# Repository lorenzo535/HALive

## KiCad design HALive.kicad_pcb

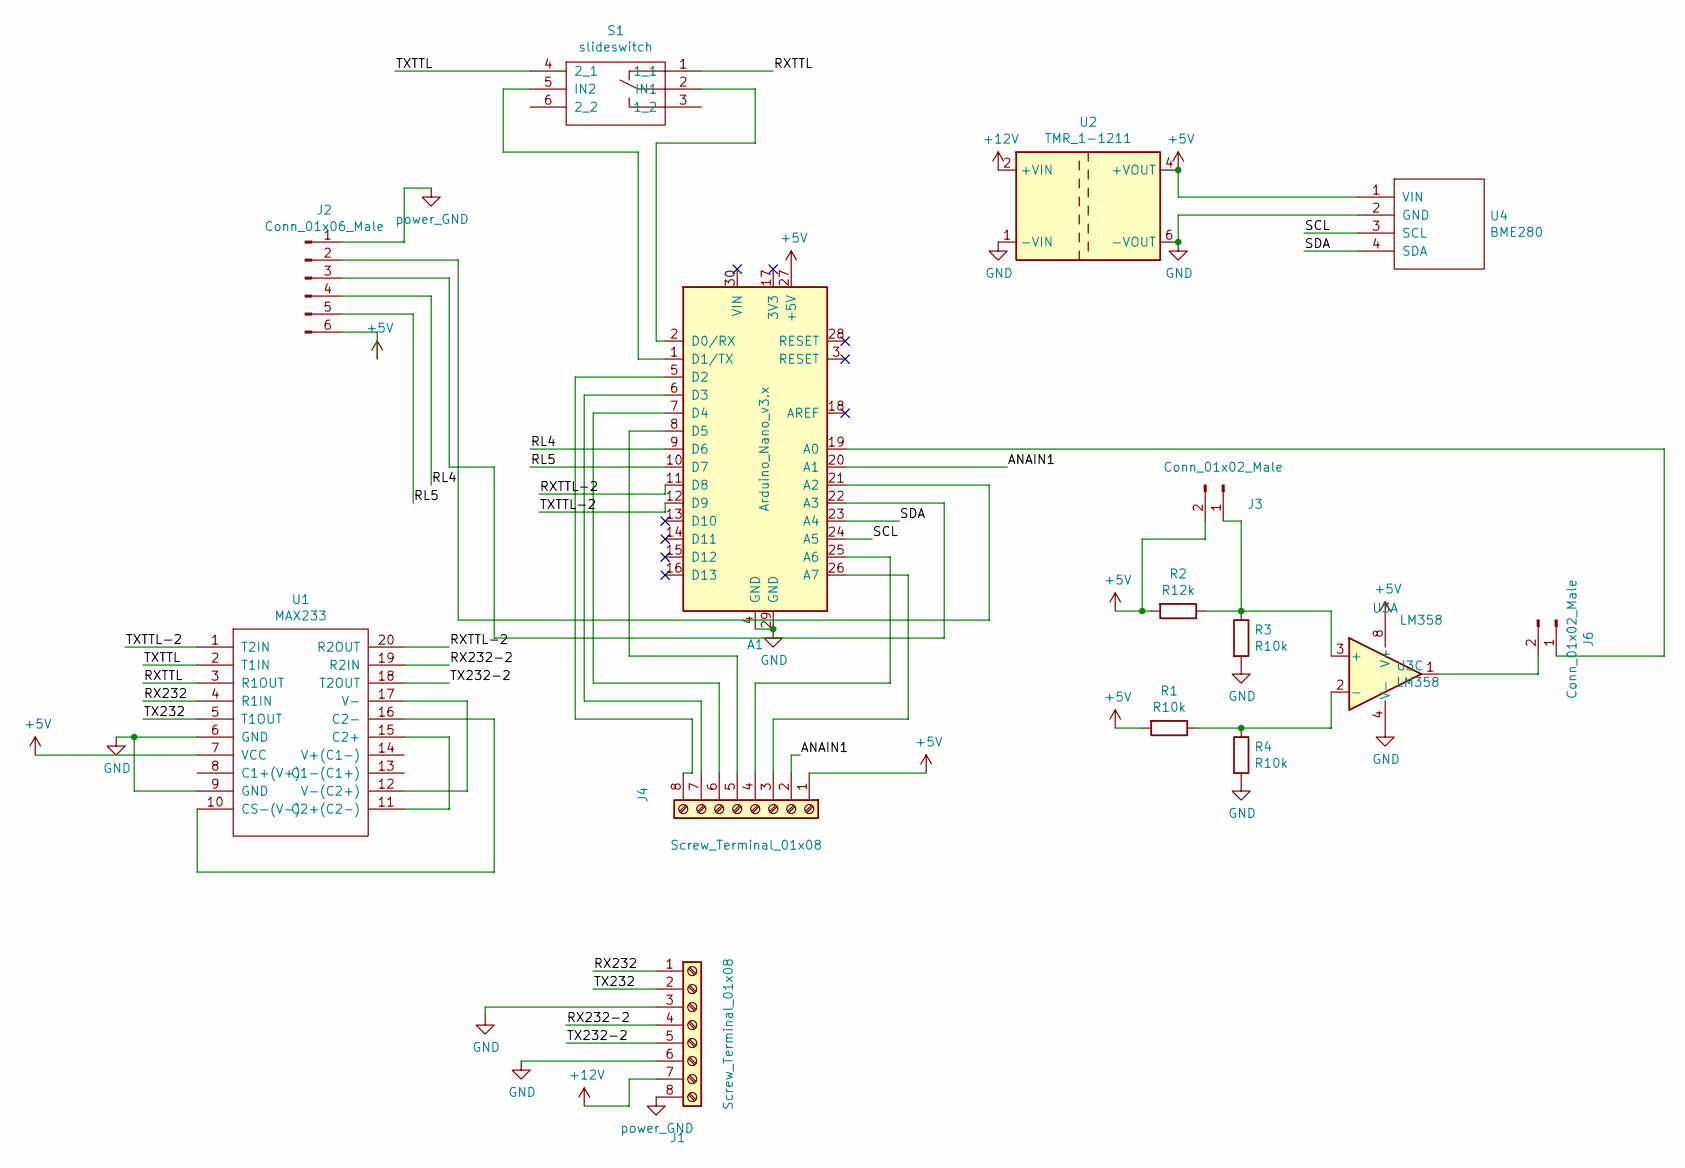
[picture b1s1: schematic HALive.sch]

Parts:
A1: Arduino_Nano_v3.x; Arduino_Nano
J1, J4: Screw_Terminal_01x08; PhoenixContact_MCV_1,5_8-G-3.5_1x08_P3.50mm_Vertical
J2: Conn_01x06_Male; PinHeader_1x06_P2.54mm_Vertical
J3, J6: Conn_01x02_Male; PinHeader_1x02_P2.54mm_Vertical
R1, R3, R4: R10k; R_Axial_DIN0207_L6.3mm_D2.5mm_P10.16mm_Horizontal
R2: R12k; R_Axial_DIN0207_L6.3mm_D2.5mm_P10.16mm_Horizontal
S1: slideswitch; slide_sxitch_TE_ASE2204
U1: MAX233; DIP-20_W7.62mm
U2: TMR_1-1211; Converter_DCDC_TRACO_TMR-1-xxxx_Single_THT
U3: LM358; DIP-8_W7.62mm
U4: BME280

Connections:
+5V: A1.27 (+5V), J2.6, J3.2, J4.1, R1.2, R2.2, U1.7 (VCC), U2.4 (+VOUT), U3.8 (V+), U4.1 (VIN)
+12V: J1.7, U2.2 (+VIN)
/ANAIN1: A1.20 (A1), J4.2
/RL4: A1.9 (D6), J2.4
/RL5: A1.10 (D7), J2.5
/RX232: J1.1, U1.4 (R1IN)
/RX232-2: J1.4, U1.19 (R2IN)
/RXTTL: S1.1 (1_1), U1.3 (R1OUT)
/RXTTL-2: A1.11 (D8), U1.20 (R2OUT)
/SCL: A1.24 (A5), U4.3 (SCL)
/SDA: A1.23 (A4), U4.4 (SDA)
/TX232: J1.2, U1.5 (T1OUT)
/TX232-2: J1.5, U1.18 (T2OUT)
/TXTTL: S1.4 (2_1), U1.2 (T1IN)
/TXTTL-2: A1.12 (D9), U1.1 (T2IN)
unnamed: A1.1 (D1/TX), S1.5 (IN2)
unnamed: A1.2 (D0/RX), S1.2 (IN1)
unnamed: A1.5 (D2), J4.8
unnamed: A1.6 (D3), J4.7
unnamed: A1.7 (D4), J4.6
unnamed: A1.8 (D5), J4.5
unnamed: A1.19 (A0), J6.1
unnamed: A1.21 (A2), J2.2
unnamed: A1.22 (A3), J2.3
unnamed: A1.25 (A6), J4.4
unnamed: A1.26 (A7), J4.3
unnamed: J3.1, R2.1, R3.1, U3.3 (+)
unnamed: J6.2, U3.1
unnamed: R1.1, R4.1, U3.2 (-)
unnamed: U1.10 (CS-(V-)), U1.16 (C2-)
unnamed: U1.11 (C2+(C2-)), U1.15 (C2+)
unnamed: U1.12 (V-(C2+)), U1.17 (V-)

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
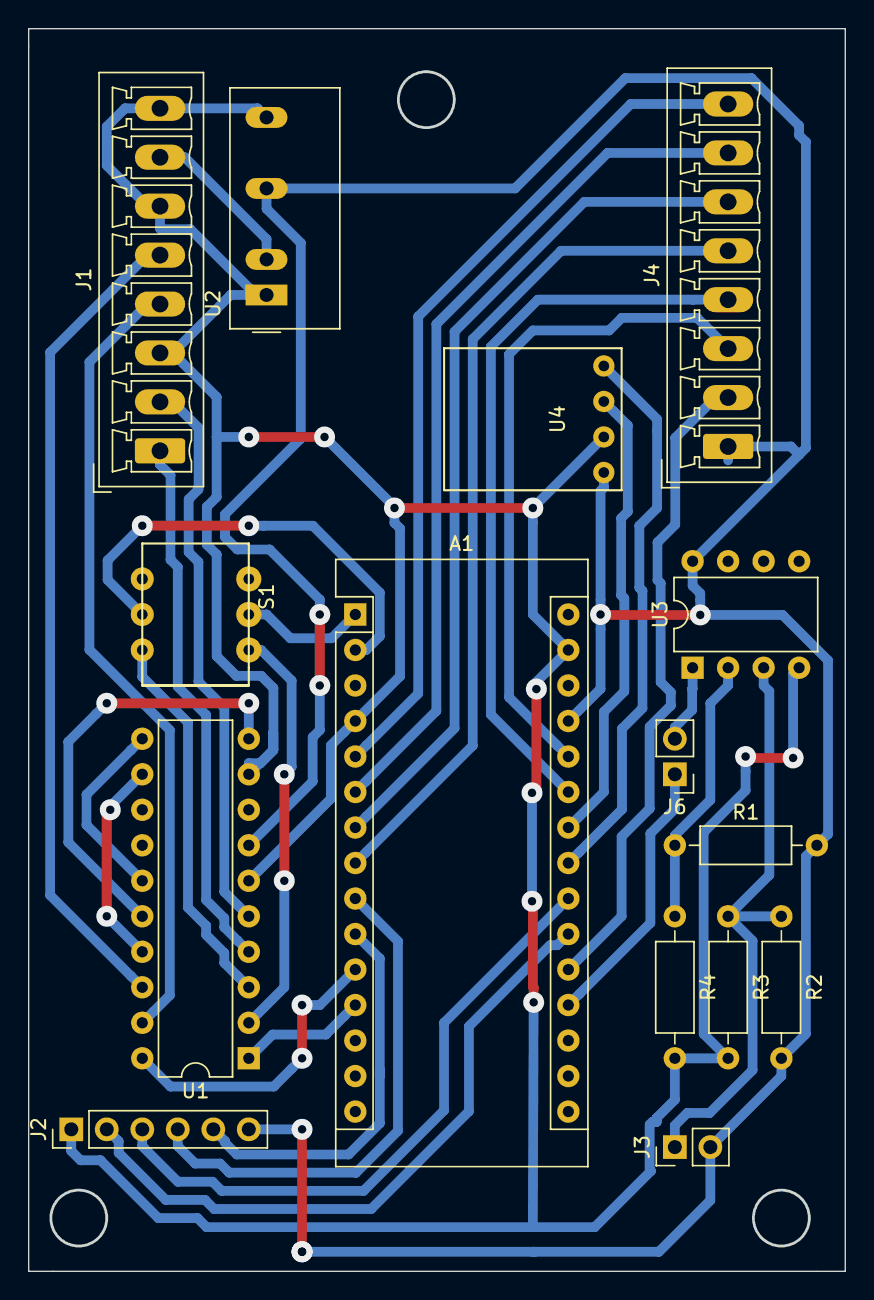
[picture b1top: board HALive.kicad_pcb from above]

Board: 2 copper layers, 58.4 x 88.9 mm, 15 parts (0 on the bottom side), 33 nets.

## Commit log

2019-07-12 routed, to be printed and tested
2019-07-12 added BEM280 sensor
2019-07-24 pcb tweaks
